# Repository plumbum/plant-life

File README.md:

Plant Life
==========

Led driver, daily timer, themperature and humidity sensors

Progress
--------

  * Led driver draft

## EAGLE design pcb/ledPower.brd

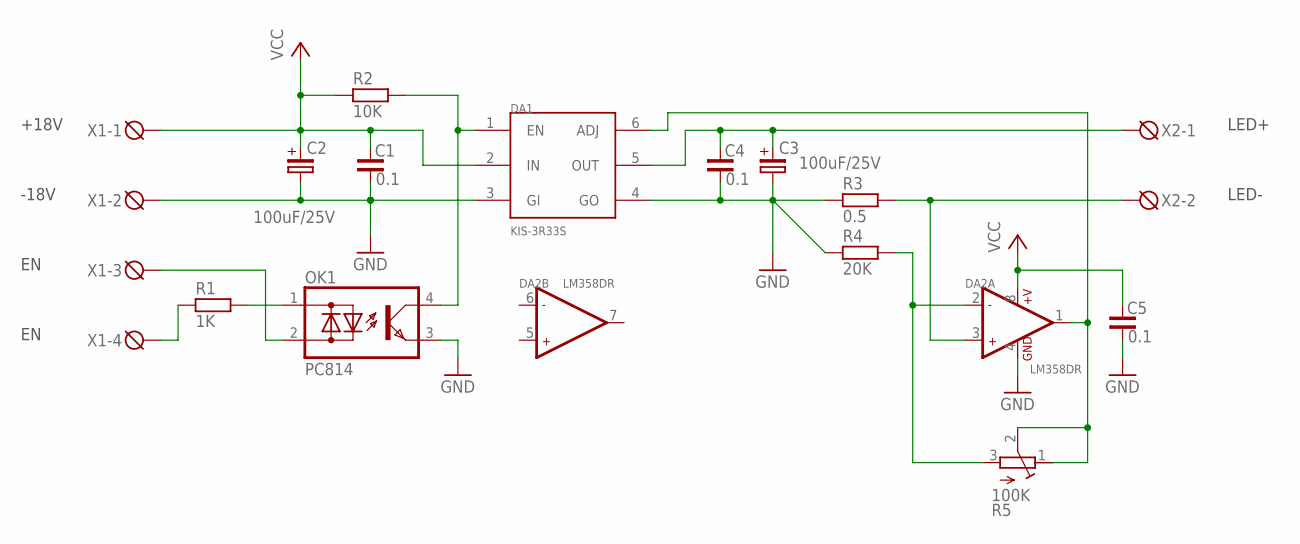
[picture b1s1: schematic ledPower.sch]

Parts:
C1, C4: 0.1; C1206
C2, C3: 100uF/25V; CE-025X060
C5: 0.1; C0805
DA1: KIS-3R33S
DA2: LM358DR; SOIC8
OK1: PC814; DIL04
R1: 1K; R0805
R2: 10K; R0805
R3: 0.5; 0414/15
R4: 20K; R0805
R5: 100K; RTRIMT93YA
X1: DG3XX-04-0.5; DG306-5.0-04P
X2: DG3XX-02-5.0; DG306-5.0-02P

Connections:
GND: C1.2, C2.-, C3.-, C4.2, C5.2, DA1.3 (GI), DA1.4 (GO), DA2.4 (GND), OK1.3 (E), R3.1, R4.1, X1.2
unnamed: R1.1, X1.4
unnamed: C3.+, C4.1, DA1.5 (OUT), X2.1
unnamed: DA1.1 (EN), OK1.4 (C), R2.2
unnamed: OK1.1 (AC1), R1.2
unnamed: OK1.2 (AC2), X1.3
unnamed: DA2.3 (+IN1), R3.2, X2.2
unnamed: DA2.2 (-IN1), R4.2, R5.3 (E)
unnamed: DA1.6 (ADJ), DA2.1 (OUT1), R5.1 (A), R5.2 (S)
VCC: C1.1, C2.+, C5.1, DA1.2 (IN), DA2.8 (+V), R2.1, X1.1

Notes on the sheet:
LED+
LED-
+18V
-18V

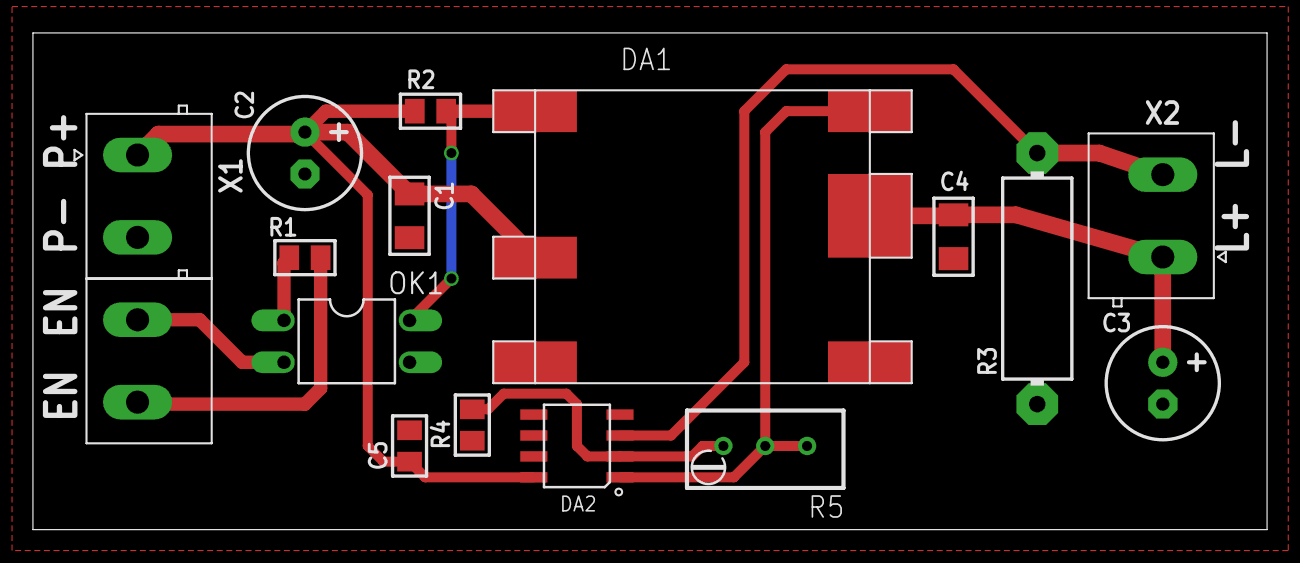
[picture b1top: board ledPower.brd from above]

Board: 2 copper layers, 74.9 x 30.1 mm, 15 parts (0 on the bottom side), 10 nets.

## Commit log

2015-09-18 led driver draft
2015-09-18 change sizes

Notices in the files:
parts and their libraries:
rc-master: Copyright (C) 2007, Bob Starr
